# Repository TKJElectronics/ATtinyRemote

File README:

The code is released under the GNU General Public License.

This is a remote translator based on an ATtiny85. It translates commands from a Panasonic remote to specific JVC commands. This enables me to turn my JVC stereo on and off, mute it and turn the volume up or down, using my Panasonic remote for my TV.

A new version is now available, it can be found in the /ATtinyRemoteVer2 folder.

For more information see my blog post: http://blog.tkjelectronics.dk/2012/03/attinyremote/ or send me an email at kristianl at tkjelectronics dot dk.

The receiving code is based around Adafruit's IR-Commander sketch: https://github.com/adafruit/IR-Commander while the decoding of the Panasonic protocol and sending of the JVC commands are based upon this forked library: https://github.com/zenwheel/Arduino-IRremote. The originally library is by Ken Shirriff: https://github.com/shirriff/Arduino-IRremote

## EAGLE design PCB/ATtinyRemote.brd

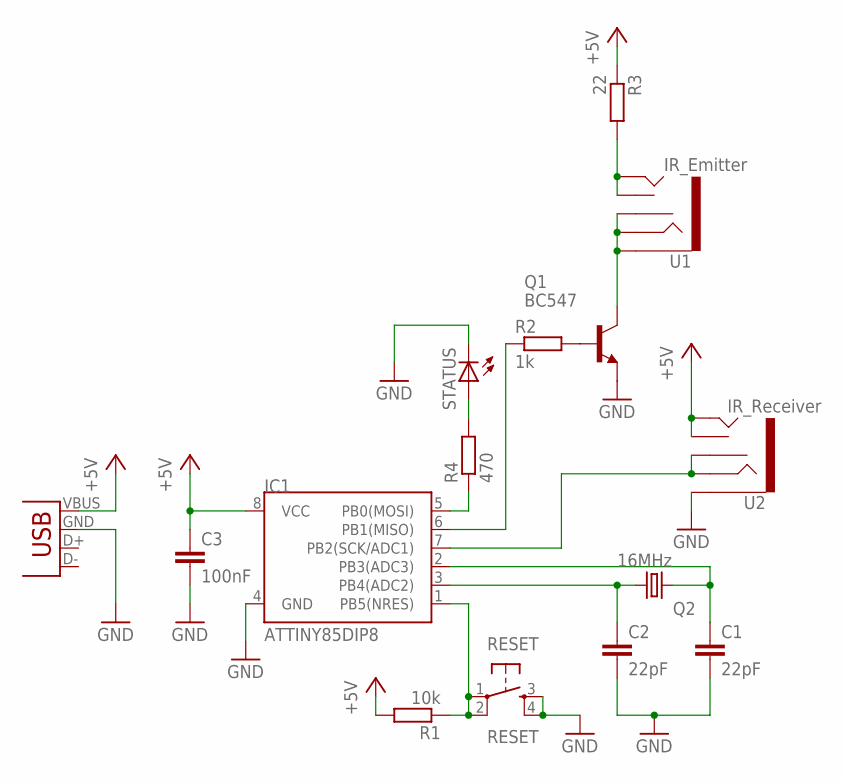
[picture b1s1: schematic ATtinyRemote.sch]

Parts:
C1, C2: 22pF; C025-025X050
C3: 100nF; C025-025X050
IC1: ATTINY85DIP8; DIP08
Q1: BC547; TO92
Q2: 16MHz; HC49/S
R1: 10k; 0207/10
R2: 1k; 0207/10
R3: 22; 0207/10
R4: 470; 0207/10
RESET: RESET; TACTILE-PTH
STATUS: LED3MM
U1: IR_Emitter; AUDIO-JACK
U2: IR_Receiver; AUDIO-JACK
X1: USB-A-H

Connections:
+5V: C3.1, IC1.8 (VCC), R1.2, R3.1, U2.TIP, U2.TSH, X1.VBUS (GND)
GND: C1.2, C2.2, C3.2, IC1.4 (GND), Q1.1 (E), RESET.3, RESET.4, STATUS.K (C), U2.SLEEVE, X1.GND (VBUS)
unnamed: C2.1, IC1.3 (PB4(ADC2)), Q2.1
unnamed: R3.2, U1.TIP, U1.TSH
unnamed: IC1.1 (PB5(NRES)), R1.1, RESET.1, RESET.2
unnamed: Q1.3 (C), U1.RING, U1.RSH, U1.SLEEVE
unnamed: IC1.7 (PB2(SCK/ADC1)), U2.RING, U2.RSH
unnamed: Q1.2 (B), R2.2
unnamed: IC1.6 (PB1(MISO)), R2.1
unnamed: R4.2, STATUS.A
unnamed: IC1.5 (PB0(MOSI)), R4.1
unnamed: C1.1, IC1.2 (PB3(ADC3)), Q2.2

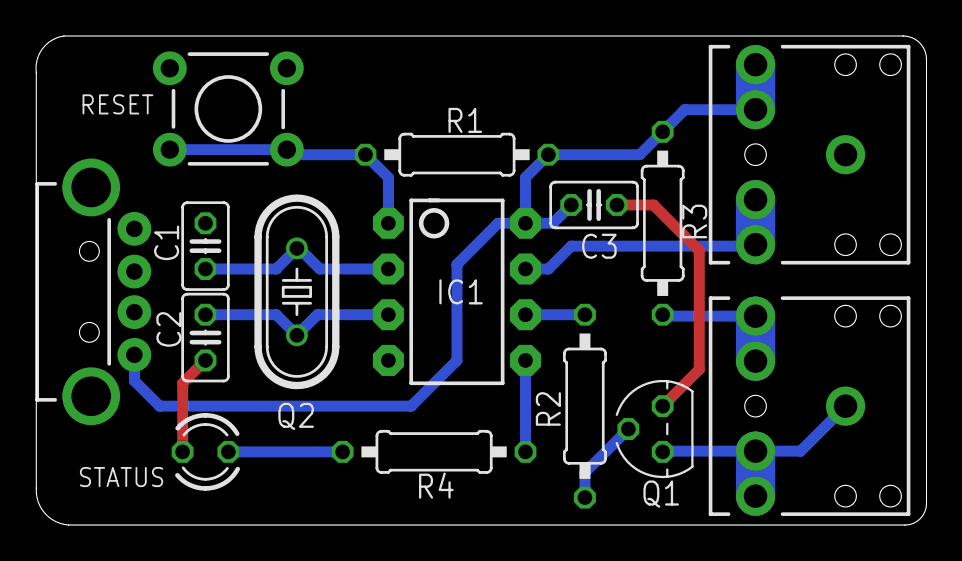
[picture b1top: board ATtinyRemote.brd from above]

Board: 2 copper layers, 49.5 x 27.2 mm, 15 parts (0 on the bottom side), 12 nets.

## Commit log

2012-01-29 README ADDED
2012-01-29 First release
2012-01-29 Fixed comment
2012-01-29 Schematic and layout added
2012-01-29 Removed inttypes.h
2012-01-30 Added disable function
2012-02-07 Minor adjustments to make it work better in practice
2012-02-07 Added header
2012-02-07 Fixed silkscreen
2012-02-07 Version 1.0 of the PCB
    Gerber files for http://www.dorkbotpdx.org/wiki/pcb_order
2012-02-10 Minor update
2012-03-11 Minor edit
2012-03-19 Added link to blog post
2012-03-24 Send multiple times when power on/off and muting
2012-05-21 A highly optimized version has been added
    use timer0. It is used in CTC (Clear Timer on Compare Match Mode) every
    6ms, as the maximum pulse i approximately 5ms. As the Panasonic
    protocol is very long (48 bits) is not necessary to check the length of
    the pulses very precisely, as my other IR remotes protocols' are only
    maximum 32 bits long. But it wouldn't be that hard to modify the code
    to work with any IR protocol.
2012-06-04 Updated newDelay()
2012-06-04 Call stack overflow has know been fixed
    The ATtiny85 sometimes freezer up - I think it ran out of RAM - I
    suspect the calling of JVCCommand() which called sendJVC() that then
    called mark() and space() several times. Therefore it has now been
    implemented in the same function.
    As a bonus, the program also works much faster now.
2012-06-05 Added watchdog timer
2012-06-05 Fixed some potential bugs
2012-06-05 Found bug that caused the hang up
    Actually the watchdog timer is not necessary, as I included it, because
    I thought that the problem might be a hang up in the newDelay function,
    but I will just keep it there anyway.
2012-06-08 Disabled delay at last reapeat
2015-08-05 Fixed bug in for loop, as 'i' was already used
2015-08-05 Fixed formatting
    No code change
2018-10-26 added attiny85 tutorial link

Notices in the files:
parts and their libraries:
SparkFun: Licensing: CC v3.0 Share-Alike You are welcome to use this library for commercial purposes.
